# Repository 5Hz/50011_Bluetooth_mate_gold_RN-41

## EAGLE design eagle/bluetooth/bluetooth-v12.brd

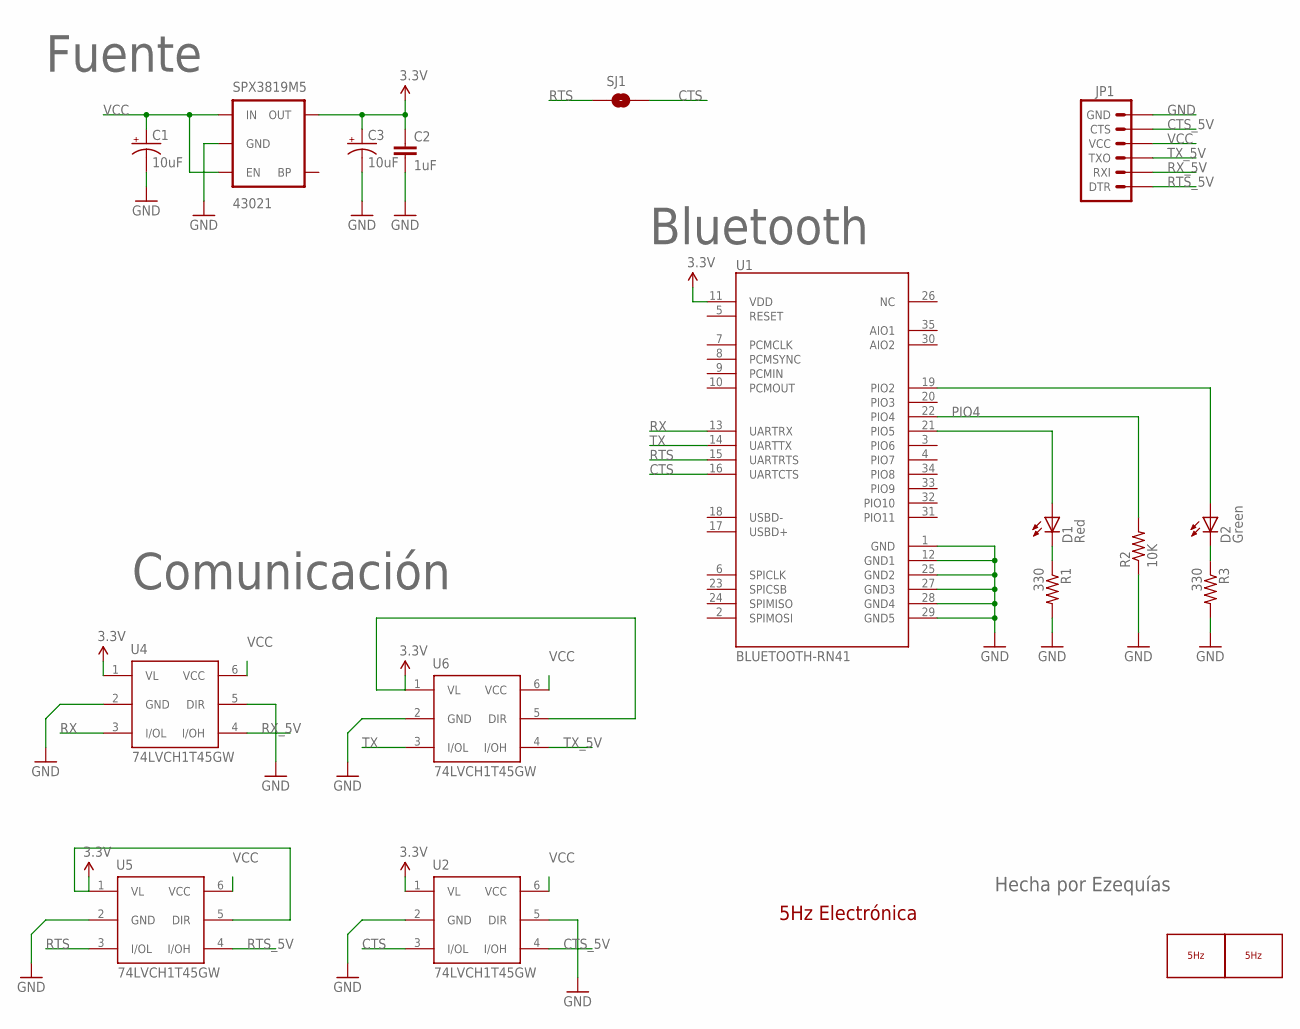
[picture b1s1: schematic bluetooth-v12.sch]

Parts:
C1, C3: 10uF; EIA3216
C2: 1uF; 0603-CAP
D1: Red; LED-0603
D2: Green; LED-0603
JP1: ARDUINO_SERIAL_PROGRAMPTH; 1X06
LOGO2: LOGO_5HZ_H_5MM; 5HZ_LOGO_H_5MM
LOGO3: LOGO_5HZ_H_15MM; 5HZ_LOGO_H_15MM
R1, R3: 330; 0603-RES
R2: 10K; 0603-RES
SJ1: SOLDERJUMPERNO; SJ_2S-NO
SPX3819M5: 43021; SOT23-5
U1: BLUETOOTH-RN41; RN41
U2, U4, U5, U6: 74LVCH1T45GW; SOT-363

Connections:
3.3V: C2.1, C3.A (+), SPX3819M5.5 (OUT), U1.11 (VDD), U2.1 (VL), U4.1 (VL), U5.1 (VL), U5.5 (DIR), U6.1 (VL), U6.5 (DIR)
CTS: SJ1.2, U1.16 (UARTCTS), U2.3 (I/OL)
CTS_5V: JP1.5 (CTS), U2.4 (I/OH)
D1: D1.C, R1.1
D2: D2.C, R3.1
GND: C1.C (-), C2.2, C3.C (-), JP1.6 (GND), R1.2, R2.1, R3.2, SPX3819M5.2 (GND), U1.1 (GND), U1.12 (GND1), U1.25 (GND2), U1.27 (GND3), U1.28 (GND4), U1.29 (GND5), U2.2 (GND), U2.5 (DIR), U4.2 (GND), U4.5 (DIR), U5.2 (GND), U6.2 (GND)
unnamed: D1.A, U1.21 (PIO5)
unnamed: D2.A, U1.19 (PIO2)
PIO4: R2.2, U1.22 (PIO4)
RTS: SJ1.1, U1.15 (UARTRTS), U5.3 (I/OL)
RTS_5V: JP1.1 (DTR), U5.4 (I/OH)
RX: U1.13 (UARTRX), U4.3 (I/OL)
RX_5V: JP1.2 (RXI), U4.4 (I/OH)
TX: U1.14 (UARTTX), U6.3 (I/OL)
TX_5V: JP1.3 (TXO), U6.4 (I/OH)
VCC: C1.A (+), JP1.4 (VCC), SPX3819M5.1 (IN), SPX3819M5.3 (EN), U2.6 (VCC), U4.6 (VCC), U5.6 (VCC), U6.6 (VCC)

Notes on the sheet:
5Hz Electrónica
Comunicación
Bluetooth
Fuente
Hecha por Ezequías

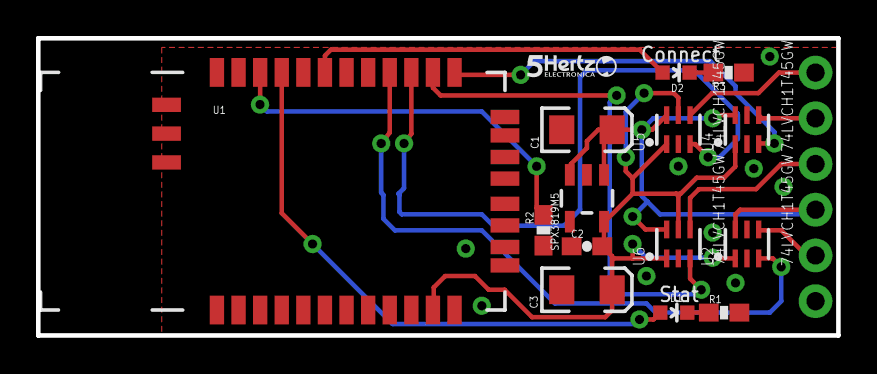
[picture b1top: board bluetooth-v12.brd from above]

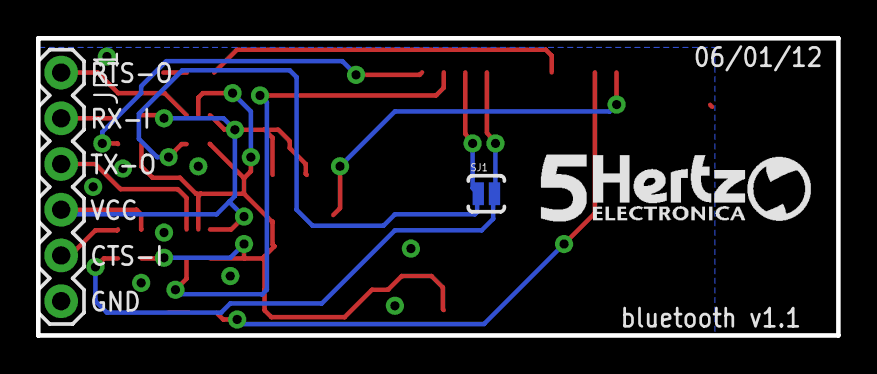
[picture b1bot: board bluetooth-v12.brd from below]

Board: 2 copper layers, 44.5 x 16.5 mm, 18 parts (3 on the bottom side), 16 nets.

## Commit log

2014-01-09 creación
